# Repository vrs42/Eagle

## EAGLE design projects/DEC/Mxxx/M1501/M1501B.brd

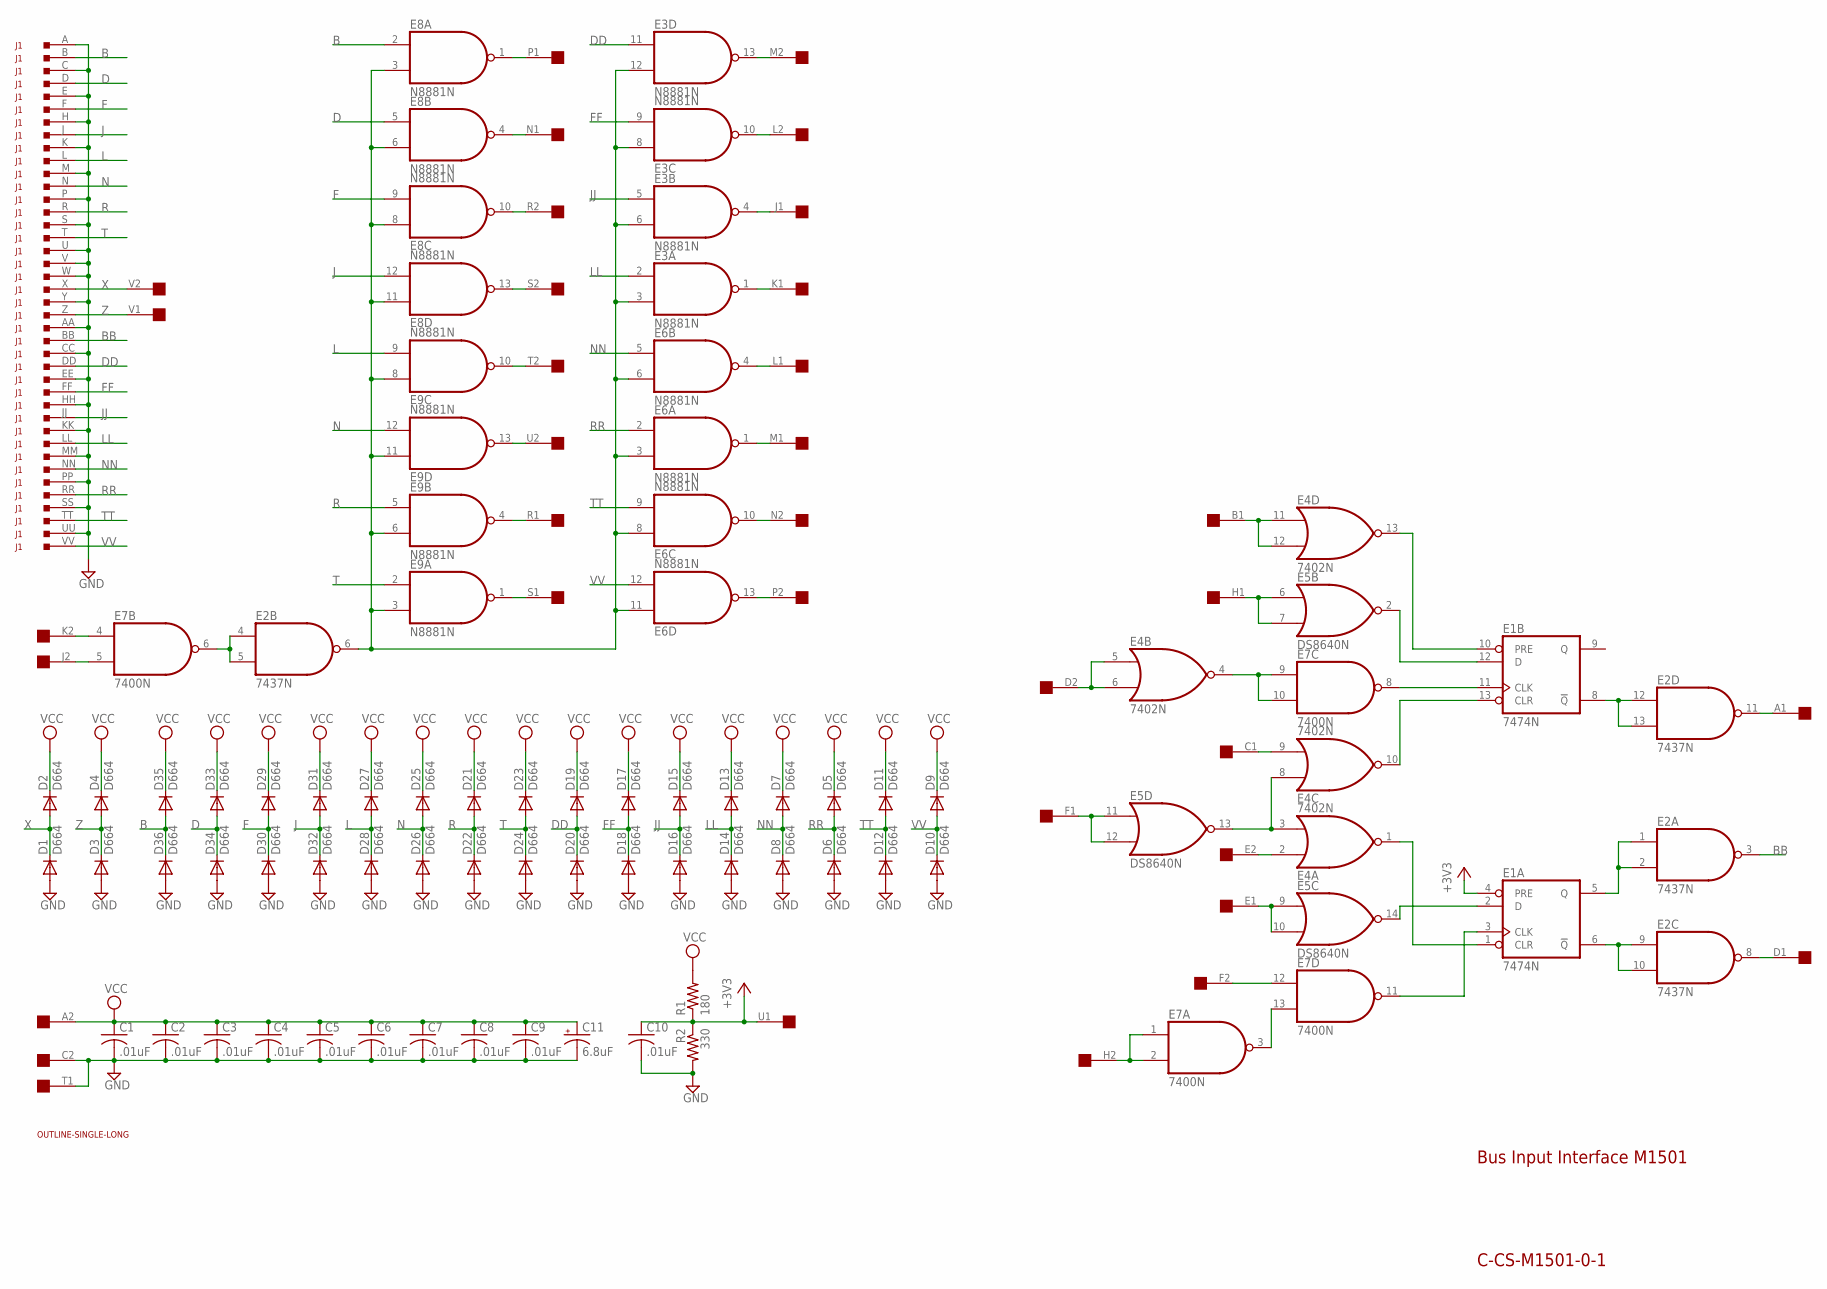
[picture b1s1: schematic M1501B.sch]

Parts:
C1, C2, C3, C4, C5, C6, C7, C8, C9, C10: .01uF; C050-025X075
C11: 6.8uF; E12-8
D1, D2, D3, D4, D5, D6, D7, D8, D9, D10, D11, D12, D13, D14, D15, D16, D17, D18, D19, D20, D21, D22, D23, D24, D25, D26, D27, D28, D29, D30, D31, D32, D33, D34, D35, D36: D664; DO35-10
E1: 7474N; DIL14
E2: 7437N; DIL14
E3, E6, E8, E9: N8881N; DIL14
E4: 7402N; DIL14
E5: DS8640N; DIL14
E7: 7400N; DIL14
J1: DEC40PINSH; DEC40PINH
R1: 180; 0207/10
R2: 330; 0207/10
U$1: OUTLINE-SINGLE-LONG; SINGLE-LONG
U$2: SINGLE; EDGE-CON2

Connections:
+3V3: C10.1, E1.4 (PRE), R1.1, R2.1, U$2.U1
A1: E2.11 (O), U$2.A1
B: D35.A, D36.C, E8.2 (I0), J1.B
B1: E4.11 (I0), E4.12 (I1), U$2.B1
BB: E2.3 (O), J1.BB
C1: E4.9 (I1), U$2.C1
D: D33.A, D34.C, E8.5 (I0), J1.D
D1: E2.8 (O), U$2.D1
D2: E4.5 (I0), E4.6 (I1), U$2.D2
DD: D19.A, D20.C, E3.11 (I0), J1.DD
E1: E5.9 (I0), E5.10 (I1), U$2.E1
E2: E4.2 (I0), U$2.E2
F: D29.A, D30.C, E8.9 (I1), J1.F
F1: E5.11 (I0), E5.12 (I1), U$2.F1
F2: E7.12 (I0), U$2.F2
FF: D17.A, D18.C, E3.9 (I1), J1.FF
GND: C1.2, C2.2, C3.2, C4.2, C5.2, C6.2, C7.2, C8.2, C9.2, C10.2, C11.-, D1.A, D3.A, D6.A, D8.A, D10.A, D12.A, D14.A, D16.A, D18.A, D20.A, D22.A, D24.A, D26.A, D28.A, D30.A, D32.A, D34.A, D36.A, E1.7 (GND), E2.7 (GND), E3.7 (GND), E4.7 (GND), E5.1 (GND), E6.7 (GND), E7.7 (GND), E8.7 (GND), E9.7 (GND), J1.A, J1.AA, J1.C, J1.CC, J1.E, J1.EE, J1.H, J1.HH, J1.K, J1.KK, J1.M, J1.MM, J1.P, J1.PP, J1.S, J1.SS, J1.U, J1.UU, J1.V, J1.W, J1.Y, R2.2, U$2.C2, U$2.T1
H1: E5.6 (I0), E5.7 (I1), U$2.H1
H2: E7.1 (I0), E7.2 (I1), U$2.H2
J: D31.A, D32.C, E8.12 (I1), J1.J
J1: E3.4 (O), U$2.J1
J2: E7.5 (I1), U$2.J2
JJ: D15.A, D16.C, E3.5 (I0), J1.JJ
K1: E3.1 (O), U$2.K1
K2: E7.4 (I0), U$2.K2
L: D27.A, D28.C, E9.9 (I1), J1.L
L1: E6.4 (O), U$2.L1
L2: E3.10 (O), U$2.L2
LL: D13.A, D14.C, E3.2 (I0), J1.LL
M1: E6.1 (O), U$2.M1
M2: E3.13 (O), U$2.M2
N: D25.A, D26.C, E9.12 (I1), J1.N
N1: E8.4 (O), U$2.N1
N2: E6.10 (O), U$2.N2
unnamed: E2.4 (I0), E2.5 (I1), E7.6 (O)
unnamed: E1.11 (CLK), E7.8 (O)
unnamed: E7.3 (O), E7.13 (I1)
unnamed: E4.4 (O), E7.9 (I0), E7.10 (I1)
unnamed: E1.3 (CLK), E7.11 (O)
unnamed: E1.5 (Q), E2.1 (I0), E2.2 (I1)
unnamed: E1.2 (D), E5.14 (O)
unnamed: E1.12 (D), E5.2 (O)
unnamed: E2.6 (O), E3.3 (I1), E3.6 (I1), E3.8 (I0), E3.12 (I1), E6.3 (I1), E6.6 (I1), E6.8 (I0), E6.11 (I0), E8.3 (I1), E8.6 (I1), E8.8 (I0), E8.11 (I0), E9.3 (I1), E9.6 (I1), E9.8 (I0), E9.11 (I0)
unnamed: E1.13 (CLR), E4.10 (O)
unnamed: E1.10 (PRE), E4.13 (O)
unnamed: E1.1 (CLR), E4.1 (O)
unnamed: E1.6 (!Q), E2.9 (I0), E2.10 (I1)
unnamed: E1.8 (!Q), E2.12 (I0), E2.13 (I1)
unnamed: E4.3 (I1), E4.8 (I0), E5.13 (O)
NN: D7.A, D8.C, E6.5 (I0), J1.NN
P1: E8.1 (O), U$2.P1
P2: E6.13 (O), U$2.P2
R: D21.A, D22.C, E9.5 (I0), J1.R
R1: E9.4 (O), U$2.R1
R2: E8.10 (O), U$2.R2
RR: D5.A, D6.C, E6.2 (I0), J1.RR
S1: E9.1 (O), U$2.S1
S2: E8.13 (O), U$2.S2
T: D23.A, D24.C, E9.2 (I0), J1.T
T2: E9.10 (O), U$2.T2
TT: D11.A, D12.C, E6.9 (I1), J1.TT
U2: E9.13 (O), U$2.U2
VCC: C1.1, C2.1, C3.1, C4.1, C5.1, C6.1, C7.1, C8.1, C9.1, C11.+, D2.C, D4.C, D5.C, D7.C, D9.C, D11.C, D13.C, D15.C, D17.C, D19.C, D21.C, D23.C, D25.C, D27.C, D29.C, D31.C, D33.C, D35.C, E1.14 (VCC), E2.14 (VCC), E3.14 (VCC), E4.14 (VCC), E5.8 (VCC), E6.14 (VCC), E7.14 (VCC), E8.14 (VCC), E9.14 (VCC), R1.2, U$2.A2
VV: D9.A, D10.C, E6.12 (I1), J1.VV
X: D1.C, D2.A, J1.X, U$2.V2
Z: D3.C, D4.A, J1.Z, U$2.V1

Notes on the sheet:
C-CS-M1501-0-1
Bus Input Interface M1501

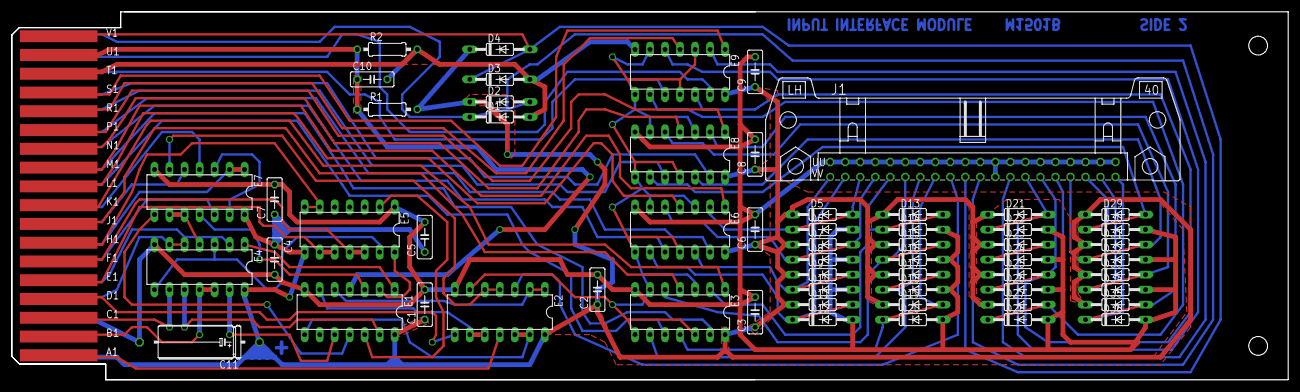
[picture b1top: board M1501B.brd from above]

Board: 2 copper layers, 215.9 x 62.2 mm, 61 parts (0 on the bottom side), 66 nets.

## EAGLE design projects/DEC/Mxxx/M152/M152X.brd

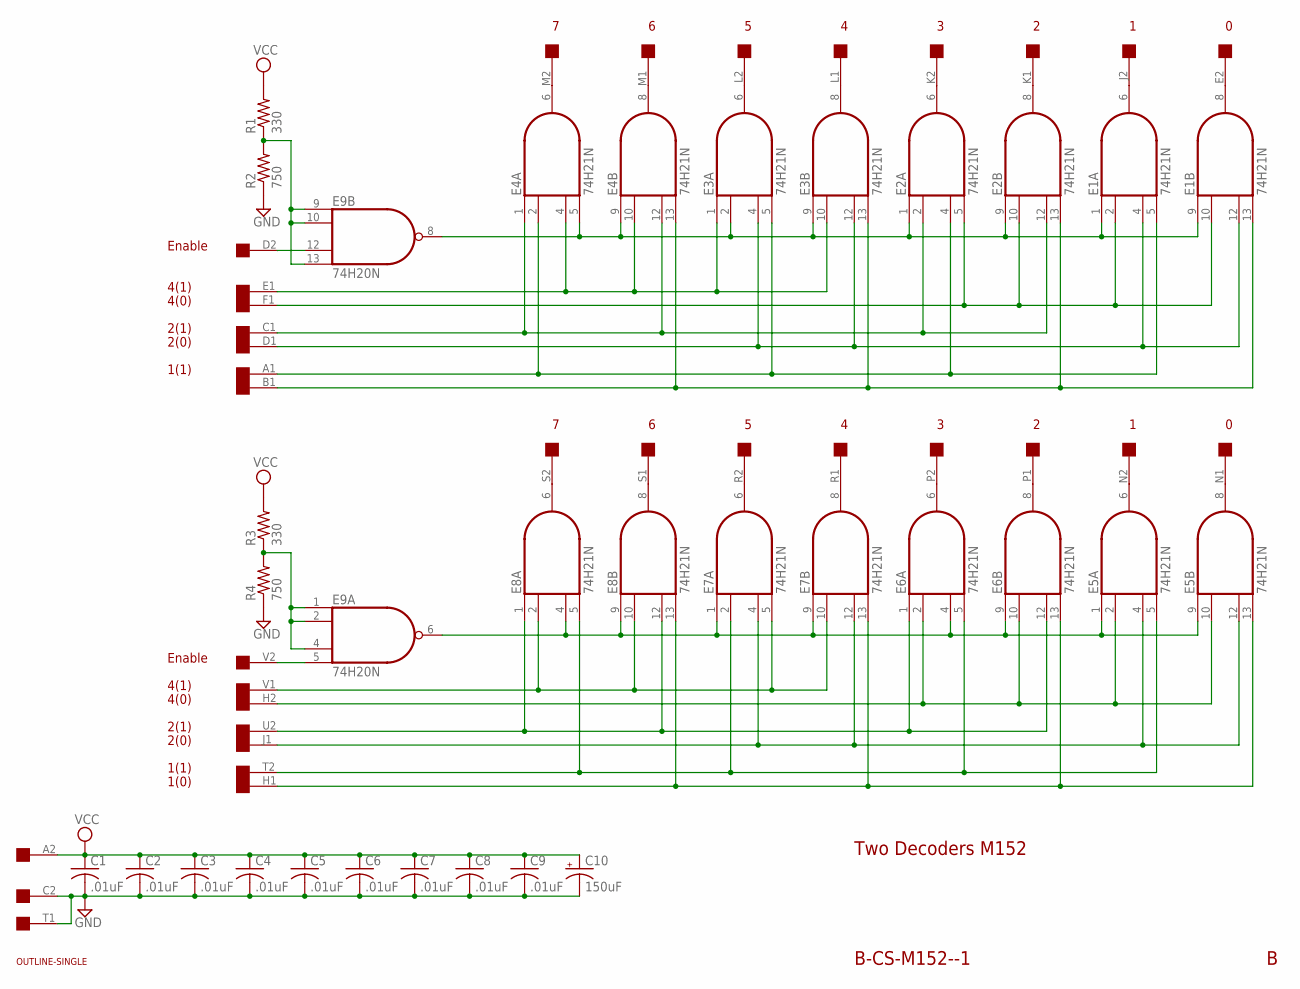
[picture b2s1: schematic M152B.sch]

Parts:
C1, C2, C3, C4, C5, C6, C7, C8, C9: .01uF; C050-025X075
C10: 150uF; E25-9
E1, E2, E3, E4, E5, E6, E7, E8: 74H21N; DIL14
E9: 74H20N; DIL14
R1, R3: 330; 0207/10
R2, R4: 750; 0207/10
U$1: SINGLE; EDGE-CON2
U$2: OUTLINE-SINGLE; SINGLE

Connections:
GND: C1.2, C2.2, C3.2, C4.2, C5.2, C6.2, C7.2, C8.2, C9.2, C10.-, E1.7 (GND), E2.7 (GND), E3.7 (GND), E4.7 (GND), E5.7 (GND), E6.7 (GND), E7.7 (GND), E8.7 (GND), E9.7 (GND), R2.1, R4.1, U$1.C2, U$1.T1
unnamed: E9.9 (I0), E9.10 (I1), E9.13 (I3), R1.1, R2.2
unnamed: E9.1 (I0), E9.2 (I1), E9.4 (I2), R3.1, R4.2
unnamed: E9.12 (I2), U$1.D2
unnamed: E9.5 (I3), U$1.V2
unnamed: E4.6 (O), U$1.M2
unnamed: E4.8 (O), U$1.M1
unnamed: E3.6 (O), U$1.L2
unnamed: E3.8 (O), U$1.L1
unnamed: E2.6 (O), U$1.K2
unnamed: E2.8 (O), U$1.K1
unnamed: E1.6 (O), U$1.J2
unnamed: E1.8 (O), U$1.E2
unnamed: E8.6 (O), U$1.S2
unnamed: E8.8 (O), U$1.S1
unnamed: E7.6 (O), U$1.R2
unnamed: E6.6 (O), U$1.P2
unnamed: E5.6 (O), U$1.N2
unnamed: E5.8 (O), U$1.N1
unnamed: E6.8 (O), U$1.P1
unnamed: E7.8 (O), U$1.R1
unnamed: E1.1 (I0), E1.9 (I0), E2.1 (I0), E2.9 (I0), E3.2 (I1), E3.9 (I0), E4.5 (I3), E4.9 (I0), E9.8 (O)
unnamed: E3.1 (I0), E3.10 (I1), E4.4 (I2), E4.10 (I1), U$1.E1
unnamed: E1.2 (I1), E1.10 (I1), E2.5 (I3), E2.10 (I1), U$1.F1
unnamed: E2.2 (I1), E2.12 (I2), E4.1 (I0), E4.12 (I2), U$1.C1
unnamed: E1.4 (I2), E1.12 (I2), E3.4 (I2), E3.12 (I2), U$1.D1
unnamed: E1.5 (I3), E2.4 (I2), E3.5 (I3), E4.2 (I1), U$1.A1
unnamed: E1.13 (I3), E2.13 (I3), E3.13 (I3), E4.13 (I3), U$1.B1
unnamed: E5.1 (I0), E5.9 (I0), E6.4 (I2), E6.9 (I0), E7.1 (I0), E7.9 (I0), E8.4 (I2), E8.9 (I0), E9.6 (O)
unnamed: E7.5 (I3), E7.10 (I1), E8.2 (I1), E8.10 (I1), U$1.V1
unnamed: E5.2 (I1), E5.10 (I1), E6.2 (I1), E6.10 (I1), U$1.H2
unnamed: E5.4 (I2), E5.12 (I2), E7.4 (I2), E7.12 (I2), U$1.J1
unnamed: E5.5 (I3), E6.5 (I3), E7.2 (I1), E8.5 (I3), U$1.T2
unnamed: E5.13 (I3), E6.13 (I3), E7.13 (I3), E8.13 (I3), U$1.H1
unnamed: E6.1 (I0), E6.12 (I2), E8.1 (I0), E8.12 (I2), U$1.U2
VCC: C1.1, C2.1, C3.1, C4.1, C5.1, C6.1, C7.1, C8.1, C9.1, C10.+, E1.14 (VCC), E2.14 (VCC), E3.14 (VCC), E4.14 (VCC), E5.14 (VCC), E6.14 (VCC), E7.14 (VCC), E8.14 (VCC), E9.14 (VCC), R1.2, R3.2, U$1.A2

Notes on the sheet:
Enable
4(1)
4(0)
2(0)
2(1)
1(1)
1(0)
Two Decoders M152
B-CS-M152--1

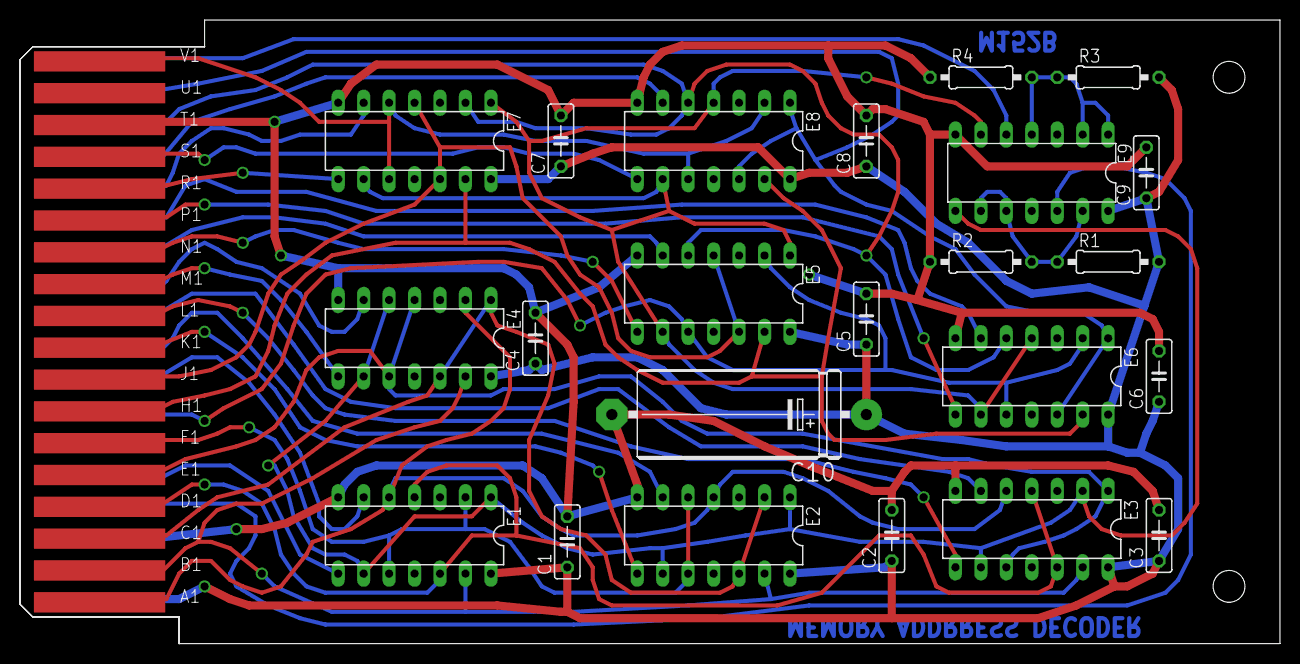
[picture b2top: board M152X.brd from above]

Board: 2 copper layers, 125.7 x 62.2 mm, 25 parts (0 on the bottom side), 36 nets.

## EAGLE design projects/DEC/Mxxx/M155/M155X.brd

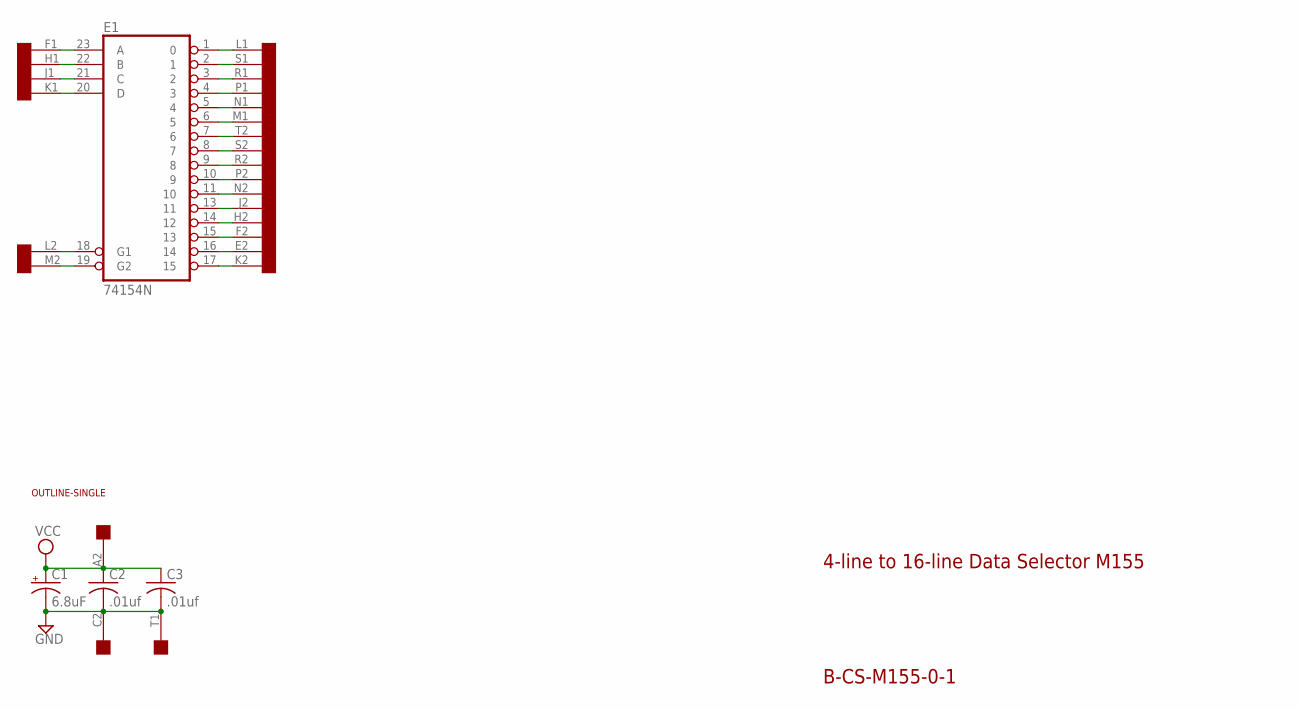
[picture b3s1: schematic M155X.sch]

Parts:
C1: 6.8uF; E22-6
C2, C3: .01uf; C050-025X075
E1: 74154N; DIL24-6
U$1: OUTLINE-SINGLE; SINGLE
U$2: EDGE-2CONNECTOR; EDGE-CON2

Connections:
GND: C1.-, C2.2, C3.2, E1.12 (GND), U$2.C2, U$2.T1
unnamed: E1.8 (7), U$2.S2
unnamed: E1.6 (5), U$2.M1
unnamed: E1.5 (4), U$2.N1
unnamed: E1.4 (3), U$2.P1
unnamed: E1.3 (2), U$2.R1
unnamed: E1.2 (1), U$2.S1
unnamed: E1.10 (9), U$2.P2
unnamed: E1.23 (A), U$2.F1
unnamed: E1.1 (0), U$2.L1
unnamed: E1.22 (B), U$2.H1
unnamed: E1.20 (D), U$2.K1
unnamed: E1.21 (C), U$2.J1
unnamed: E1.19 (G2), U$2.M2
unnamed: E1.7 (6), U$2.T2
unnamed: E1.18 (G1), U$2.L2
unnamed: E1.17 (15), U$2.K2
unnamed: E1.16 (14), U$2.E2
unnamed: E1.15 (13), U$2.F2
unnamed: E1.14 (12), U$2.H2
unnamed: E1.13 (11), U$2.J2
unnamed: E1.11 (10), U$2.N2
unnamed: E1.9 (8), U$2.R2
VCC: C1.+, C2.1, C3.1, E1.24 (VCC), U$2.A2

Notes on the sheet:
B-CS-M155-0-1
4-line to 16-line Data Selector M155

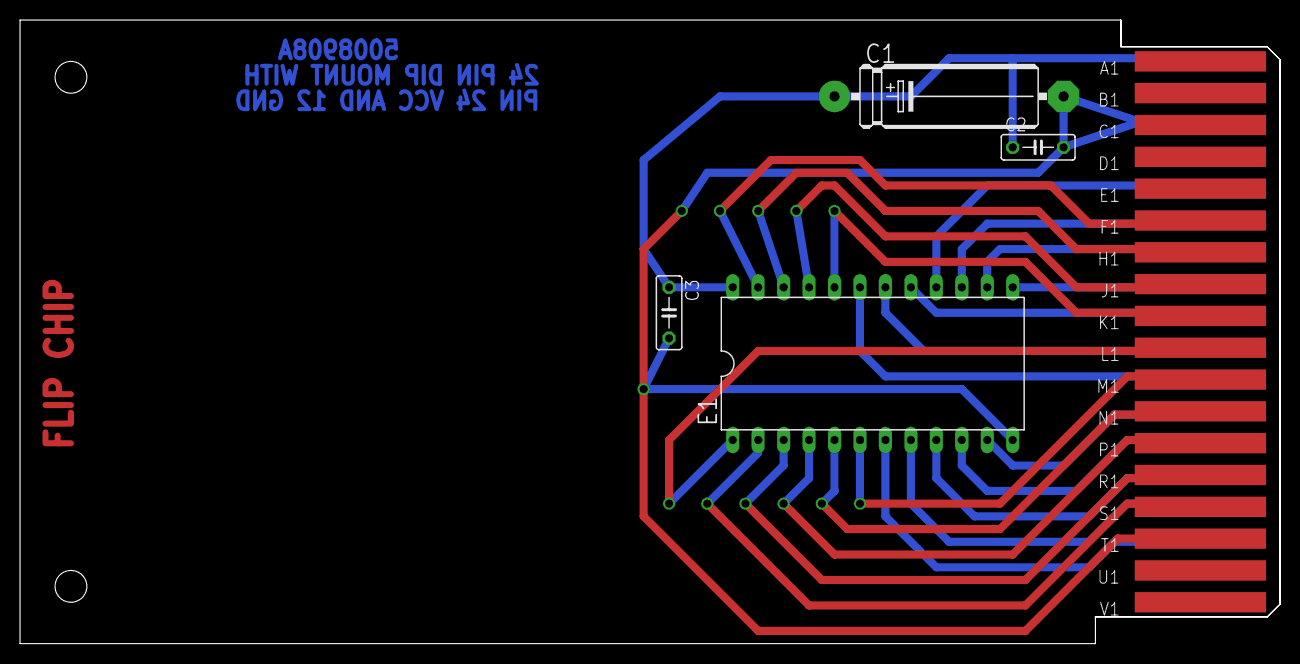
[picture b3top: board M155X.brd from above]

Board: 2 copper layers, 125.7 x 62.2 mm, 7 parts (0 on the bottom side), 24 nets.

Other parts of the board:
U$3: FLIPCHIP

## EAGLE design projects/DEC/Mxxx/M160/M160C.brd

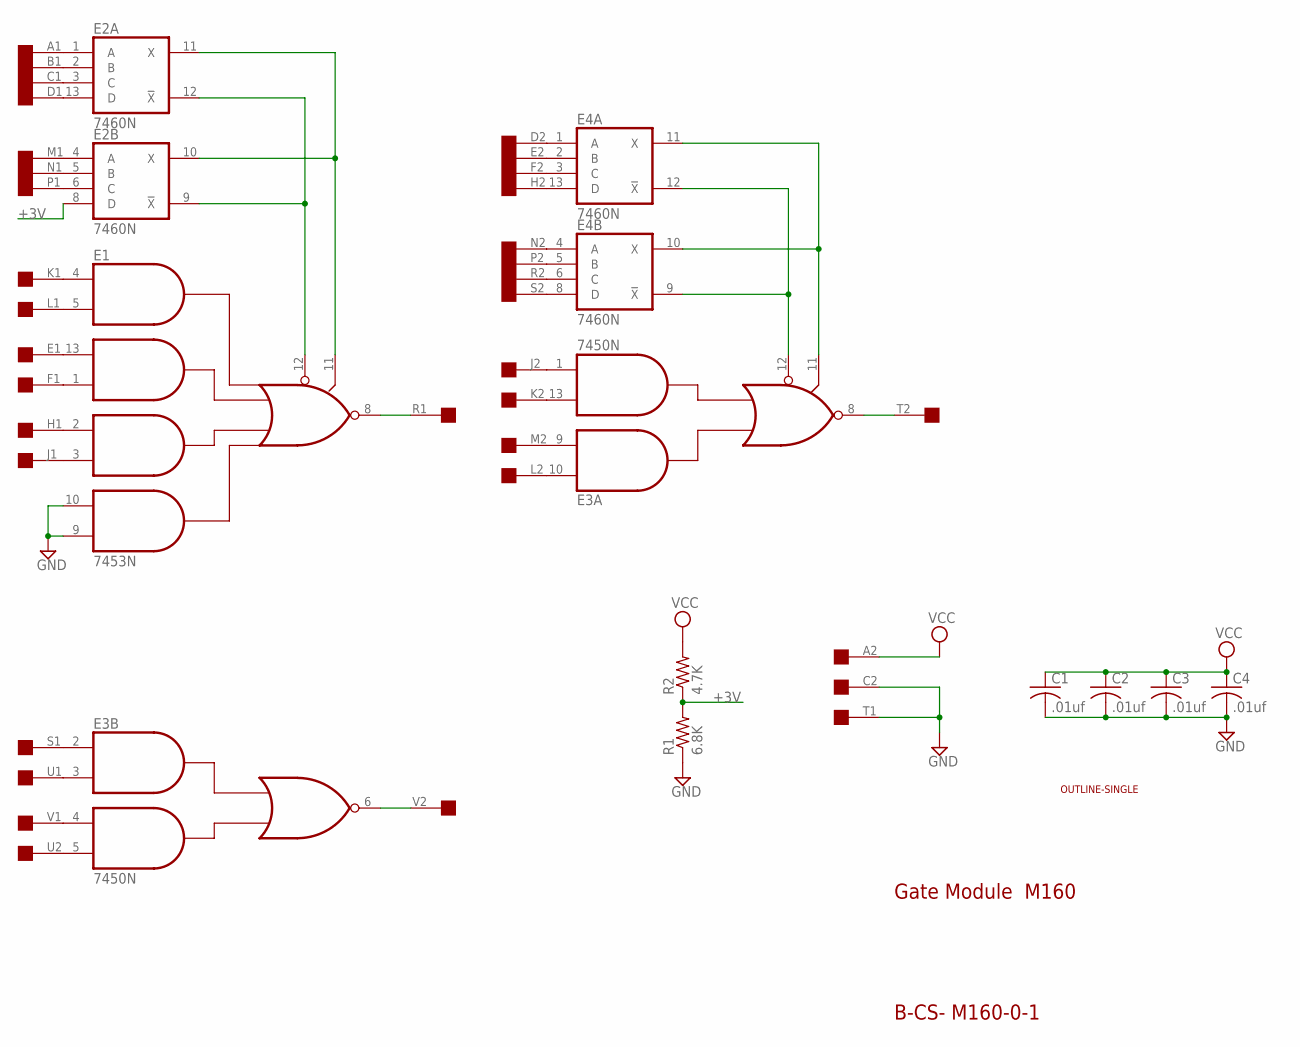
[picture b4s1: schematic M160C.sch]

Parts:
C1, C2, C3, C4: .01uf; C050-025X075
E1: 7453N; DIL14
E2, E4: 7460N; DIL14
E3: 7450N; DIL14
R1: 6.8K; 0207/10
R2: 4.7K; 0207/10
U$1: OUTLINE-SINGLE; SINGLE
U$4: SINGLE; EDGE-CON2

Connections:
+3V: E2.8 (D), R1.2, R2.1
GND: C1.2, C2.2, C3.2, C4.2, E1.7 (GND), E1.9 (I8), E1.10 (I7), E2.7 (GND), E3.7 (GND), E4.7 (GND), R1.1, U$4.C2, U$4.T1
unnamed: E1.11 (I10), E2.10 (X), E2.11 (X)
unnamed: E1.13 (I3), U$4.E1
unnamed: E1.1 (I4), U$4.F1
unnamed: E1.2 (I5), U$4.H1
unnamed: E1.3 (I6), U$4.J1
unnamed: E1.4 (I1), U$4.K1
unnamed: E1.5 (I2), U$4.L1
unnamed: E1.12 (I9), E2.9 (!X), E2.12 (!X)
unnamed: E2.1 (A), U$4.A1
unnamed: E2.2 (B), U$4.B1
unnamed: E2.3 (C), U$4.C1
unnamed: E2.13 (D), U$4.D1
unnamed: E2.6 (C), U$4.P1
unnamed: E2.5 (B), U$4.N1
unnamed: E2.4 (A), U$4.M1
unnamed: E1.8 (O), U$4.R1
unnamed: E3.10 (I1), U$4.L2
unnamed: E3.9 (I2), U$4.M2
unnamed: E3.13 (I3), U$4.K2
unnamed: E3.1 (I4), U$4.J2
unnamed: E3.12 (I5), E4.9 (!X), E4.12 (!X)
unnamed: E3.11 (I6), E4.10 (X), E4.11 (X)
unnamed: E4.3 (C), U$4.F2
unnamed: E4.2 (B), U$4.E2
unnamed: E4.1 (A), U$4.D2
unnamed: E4.13 (D), U$4.H2
unnamed: E4.4 (A), U$4.N2
unnamed: E4.6 (C), U$4.R2
unnamed: E4.8 (D), U$4.S2
unnamed: E4.5 (B), U$4.P2
unnamed: E3.8 (O), U$4.T2
unnamed: E3.2 (I1), U$4.S1
unnamed: E3.5 (I4), U$4.U2
unnamed: E3.4 (I3), U$4.V1
unnamed: E3.3 (I2), U$4.U1
unnamed: E3.6 (O), U$4.V2
VCC: C1.1, C2.1, C3.1, C4.1, E1.14 (VCC), E2.14 (VCC), E3.14 (VCC), E4.14 (VCC), R2.2, U$4.A2

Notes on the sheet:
Gate Module M160
B-CS- M160-0-1

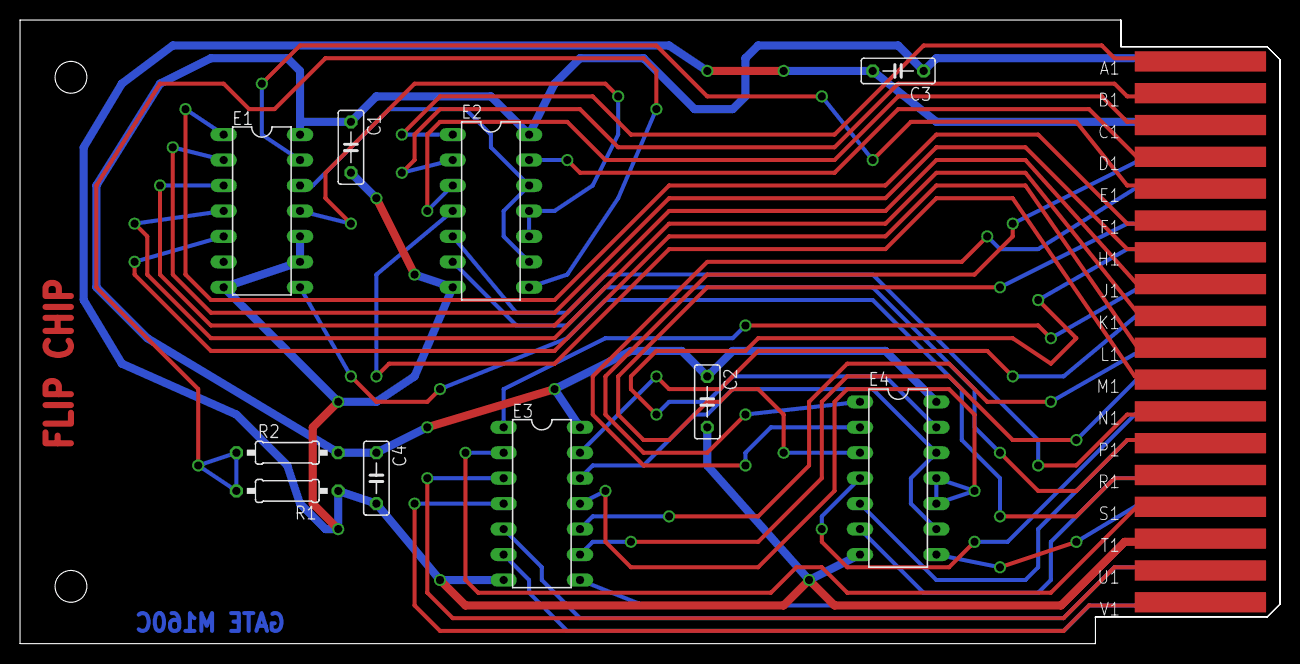
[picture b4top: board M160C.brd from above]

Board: 2 copper layers, 125.7 x 62.2 mm, 13 parts (0 on the bottom side), 39 nets.

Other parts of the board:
U$2: FLIPCHIP

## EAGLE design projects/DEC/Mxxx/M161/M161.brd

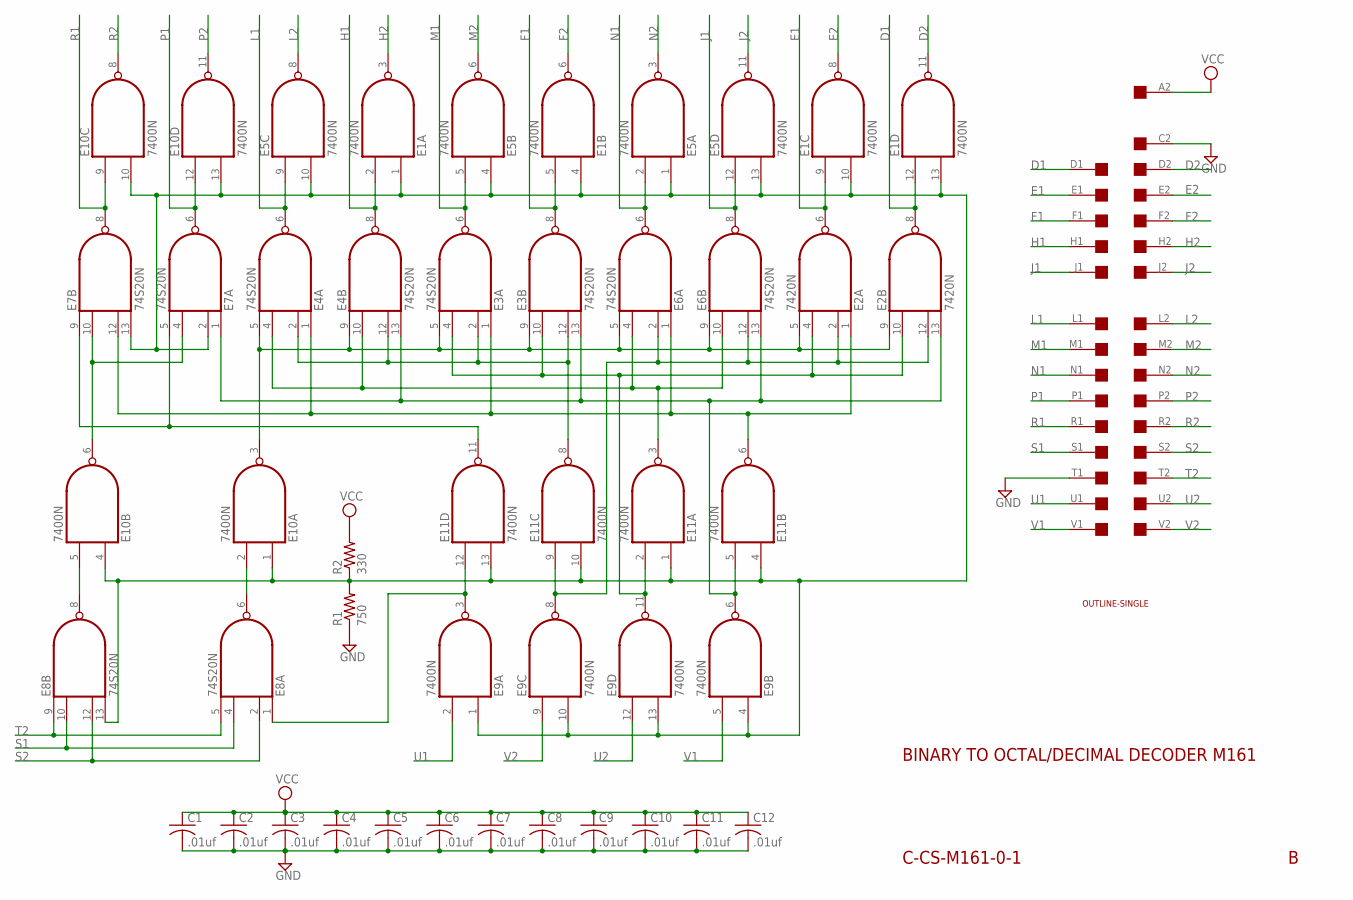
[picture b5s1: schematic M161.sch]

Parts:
C1, C2, C3, C4, C5, C6, C7, C8, C9, C10, C11, C12: .01uf; C050-025X075
E1, E5, E9, E10, E11: 7400N; DIL14
E2: 7420N; DIL14
E3, E4, E6, E7, E8: 74S20N; DIL14
R1: 750; 0207/10
R2: 330; 0207/10
U$1: OUTLINE-SINGLE; SINGLE
U$4: SINGLE; EDGE-CON2

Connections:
D1: E1.12 (I0), E2.8 (O), U$4.D1
D2: E1.11 (O), U$4.D2
E1: E1.9 (I0), E2.6 (O), U$4.E1
E2: E1.8 (O), U$4.E2
F1: E1.5 (I1), E3.8 (O), U$4.F1
F2: E1.6 (O), U$4.F2
GND: C1.2, C2.2, C3.2, C4.2, C5.2, C6.2, C7.2, C8.2, C9.2, C10.2, C11.2, C12.2, E1.7 (GND), E2.7 (GND), E3.7 (GND), E4.7 (GND), E5.7 (GND), E6.7 (GND), E7.7 (GND), E8.7 (GND), E9.7 (GND), E10.7 (GND), E11.7 (GND), R1.1, U$4.C2, U$4.T1
H1: E1.2 (I1), E4.8 (O), U$4.H1
H2: E1.3 (O), U$4.H2
J1: E5.12 (I0), E6.8 (O), U$4.J1
J2: E5.11 (O), U$4.J2
L1: E4.6 (O), E5.9 (I0), U$4.L1
L2: E5.8 (O), U$4.L2
M1: E3.6 (O), E5.5 (I1), U$4.M1
M2: E5.6 (O), U$4.M2
N1: E5.2 (I1), E6.6 (O), U$4.N1
N2: E5.3 (O), U$4.N2
unnamed: E1.1 (I0), E1.4 (I0), E1.10 (I1), E1.13 (I1), E5.1 (I0), E5.4 (I0), E5.10 (I1), E5.13 (I1), E7.2 (I1), E7.13 (I3), E8.13 (I3), E9.1 (I0), E9.4 (I0), E9.10 (I1), E9.13 (I1), E10.1 (I0), E10.4 (I0), E10.10 (I1), E10.13 (I1), E11.1 (I0), E11.4 (I0), E11.10 (I1), E11.13 (I1), R1.2, R2.1
unnamed: E8.8 (O), E10.5 (I1)
unnamed: E7.4 (I2), E7.10 (I1), E10.6 (O)
unnamed: E2.5 (I3), E2.9 (I0), E3.5 (I3), E3.9 (I0), E4.5 (I3), E4.9 (I0), E6.5 (I3), E6.9 (I0), E10.3 (O)
unnamed: E8.6 (O), E10.2 (I1)
unnamed: E8.1 (I0), E9.3 (O), E11.12 (I0)
unnamed: E2.2 (I1), E2.12 (I2), E6.2 (I1), E6.12 (I2), E9.8 (O), E11.9 (I0)
unnamed: E2.4 (I2), E2.10 (I1), E3.4 (I2), E3.10 (I1), E9.11 (O), E11.2 (I1)
unnamed: E2.13 (I3), E3.13 (I3), E4.13 (I3), E6.13 (I3), E7.1 (I0), E9.6 (O), E11.5 (I1)
unnamed: E3.2 (I1), E3.12 (I2), E4.2 (I1), E4.12 (I2), E11.8 (O)
unnamed: E7.5 (I3), E7.9 (I0), E11.11 (O)
unnamed: E4.4 (I2), E4.10 (I1), E6.4 (I2), E6.10 (I1), E11.3 (O)
unnamed: E2.1 (I0), E3.1 (I0), E4.1 (I0), E6.1 (I0), E7.12 (I2), E11.6 (O)
P1: E7.6 (O), E10.12 (I0), U$4.P1
P2: E10.11 (O), U$4.P2
R1: E7.8 (O), E10.9 (I0), U$4.R1
R2: E10.8 (O), U$4.R2
S1: E8.4 (I2), E8.10 (I1), U$4.S1
S2: E8.2 (I1), E8.12 (I2), U$4.S2
T2: E8.5 (I3), E8.9 (I0), U$4.T2
U1: E9.2 (I1), U$4.U1
U2: E9.12 (I0), U$4.U2
V1: E9.5 (I1), U$4.V1
V2: E9.9 (I0), U$4.V2
VCC: C1.1, C2.1, C3.1, C4.1, C5.1, C6.1, C7.1, C8.1, C9.1, C10.1, C11.1, C12.1, E1.14 (VCC), E2.14 (VCC), E3.14 (VCC), E4.14 (VCC), E5.14 (VCC), E6.14 (VCC), E7.14 (VCC), E8.14 (VCC), E9.14 (VCC), E10.14 (VCC), E11.14 (VCC), R2.2, U$4.A2

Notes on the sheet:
BINARY TO OCTAL/DECIMAL DECODER M161
C-CS-M161-0-1

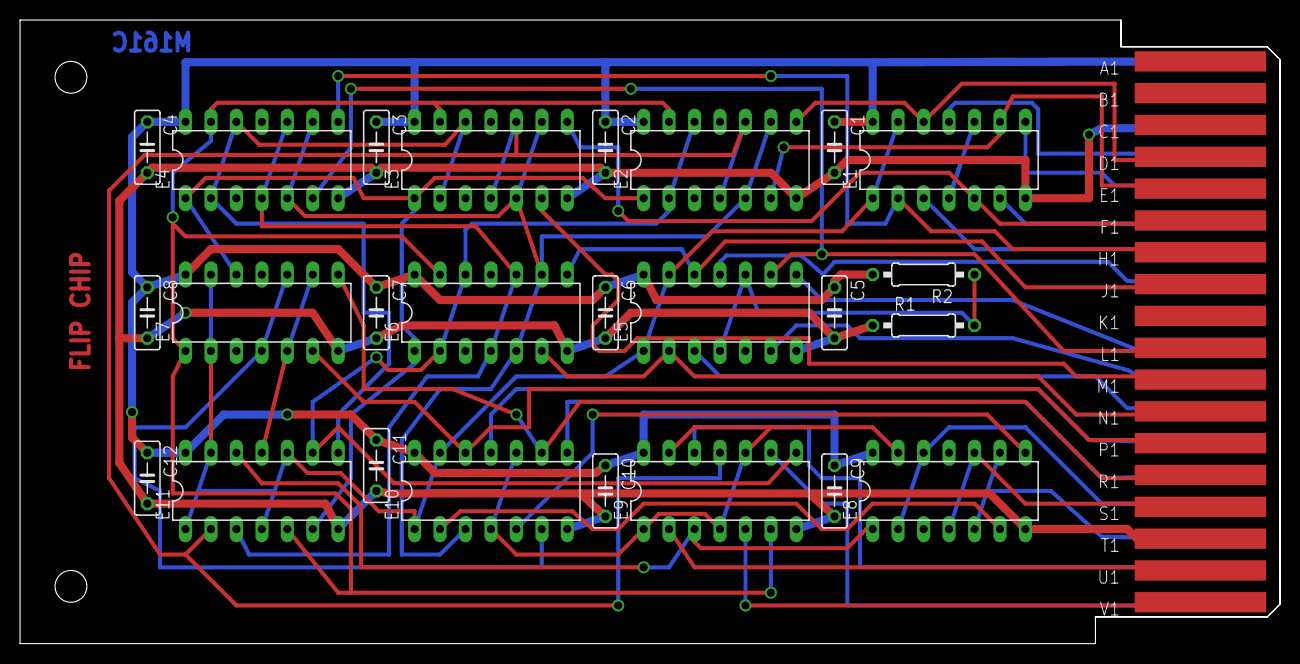
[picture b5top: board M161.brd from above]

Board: 2 copper layers, 125.7 x 62.2 mm, 27 parts (0 on the bottom side), 42 nets.
